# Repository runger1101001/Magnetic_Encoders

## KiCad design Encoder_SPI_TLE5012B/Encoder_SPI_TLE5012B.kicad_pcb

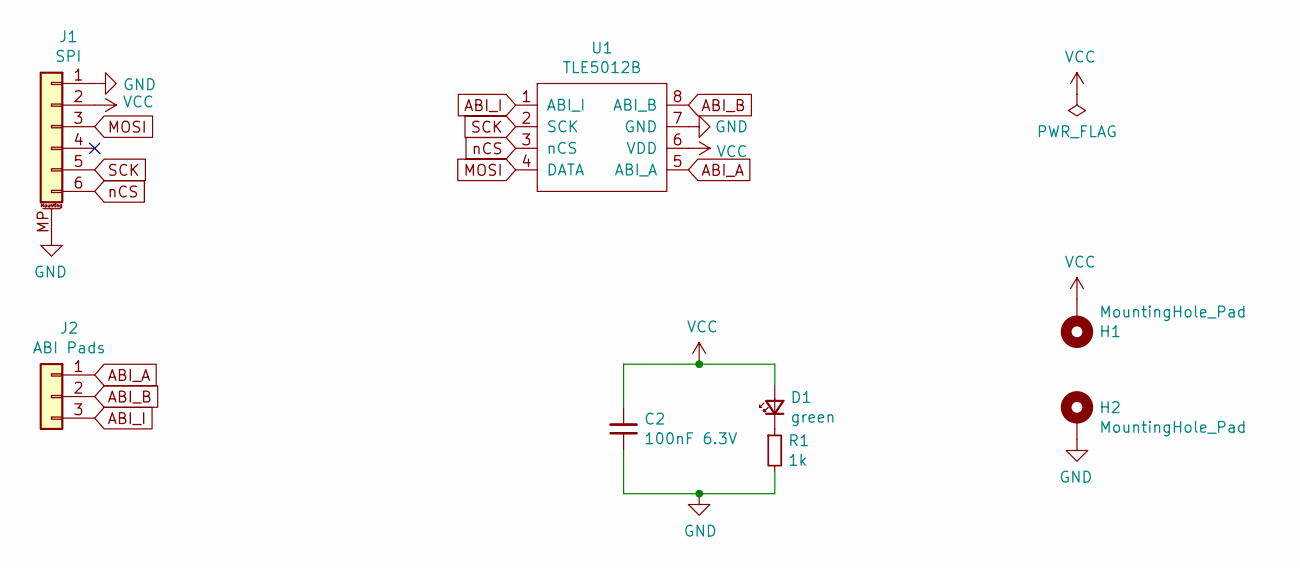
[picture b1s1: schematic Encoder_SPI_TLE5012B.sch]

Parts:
C2: 100nF 6.3V; C_0402_1005Metric; Part Generic
D1: green; LED_0402_1005Metric; Part 150040VS73240
H1, H2: MountingHole_Pad; MountingHole_2.2mm_M2_ISO7380_Pad
J1: Conn_01x06_MountingPin; JST_SH_SM06B-SRSS-TB_1x06-1MP_P1.00mm_Horizontal; Part SH_SM06B-SRSS-TB_1x06-1MP_P1.00mm_Horiz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
J2: Castellations_ABI; PinHeader_1x03_P2.54mm_Vertical
R1: 1k; R_0402_1005Metric; Part Generic 1k Resistor
U1: TLE5012B; Infineon_PG-DSO-8

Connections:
ABI_A: J2.1, U1.5 (ABI_A)
ABI_B: J2.2, U1.8 (ABI_B)
ABI_I: J2.3, U1.1 (ABI_I)
GND: C2.1, H2.1, J1.1, J1.MP (MountPin), R1.2, U1.7 (GND)
MOSI: J1.3, U1.4 (DATA)
unnamed: D1.1 (K), R1.1
SCK: J1.5, U1.2 (SCK)
VCC: C2.2, D1.2 (A), H1.1, J1.2, U1.6 (VDD)
nCS: J1.6, U1.3 (nCS)

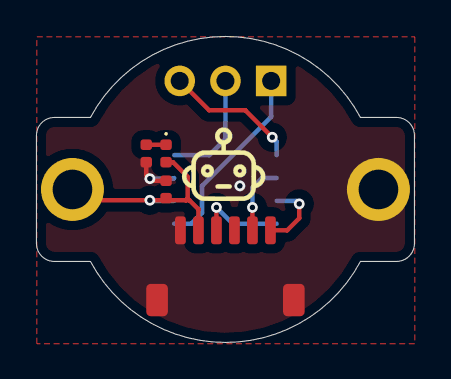
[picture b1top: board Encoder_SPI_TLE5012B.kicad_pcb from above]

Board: 2 copper layers, 21.0 x 17.0 mm, 8 parts (1 on the bottom side), 9 nets.

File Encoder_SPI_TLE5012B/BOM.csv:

"Item","Ref Des","Qty","Manufacturer","Mfg Part #","Description / Value","Package","Type","Your Instructions / Notes"
"1","C2","1","Generic","Generic","100nF 6.3V","C_0402_1005Metric","?","; Unpolarized capacitor; "
"2","D1","1","Wurth","150040VS73240","green","LED_0402_1005Metric","?","; Light emitting diode; "
"3","H2,H1","2","","Mounting Hole with connection","MountingHole_Pad","MountingHole_2.2mm_M2_ISO7380_Pad","?","; Mounting Hole with connection; "
"4","J1","1","JST","SH_SM06B-SRSS-TB_1x06-1MP_P1.00mm_Horizontal","Conn_01x06_MountingPin","JST_SH_SM06B-SRSS-TB_1x06-1MP_P1.00mm_Horizontal","?","; Generic connectable mounting pin connector, single row, 01x06, script generated (kicad-library-utils/schlib/autogen/connector/); "
"5","J2","1","","Generic connector, single row, 01x03, script generated (kicad-library-utils/schlib/autogen/connector/)","Castellations_ABI","PinHeader_1x03_P2.54mm_Vertical","?","; Generic connector, single row, 01x03, script generated (kicad-library-utils/schlib/autogen/connector/); "
"6","R1","1","Generic","Generic 1k Resistor","1k","R_0402_1005Metric","?","; Resistor; "
"7","U1","1","","TLE5012BE1000XUMA1 - 12bit SSC angle sensor","TLE5012B","Infineon_PG-DSO-8","?","; TLE5012BE1000XUMA1 - 12bit SSC angle sensor; "

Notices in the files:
Encoder_SPI_TLE5012B/Encoder_SPI_TLE5012B.kicad_pcb:
©2021
